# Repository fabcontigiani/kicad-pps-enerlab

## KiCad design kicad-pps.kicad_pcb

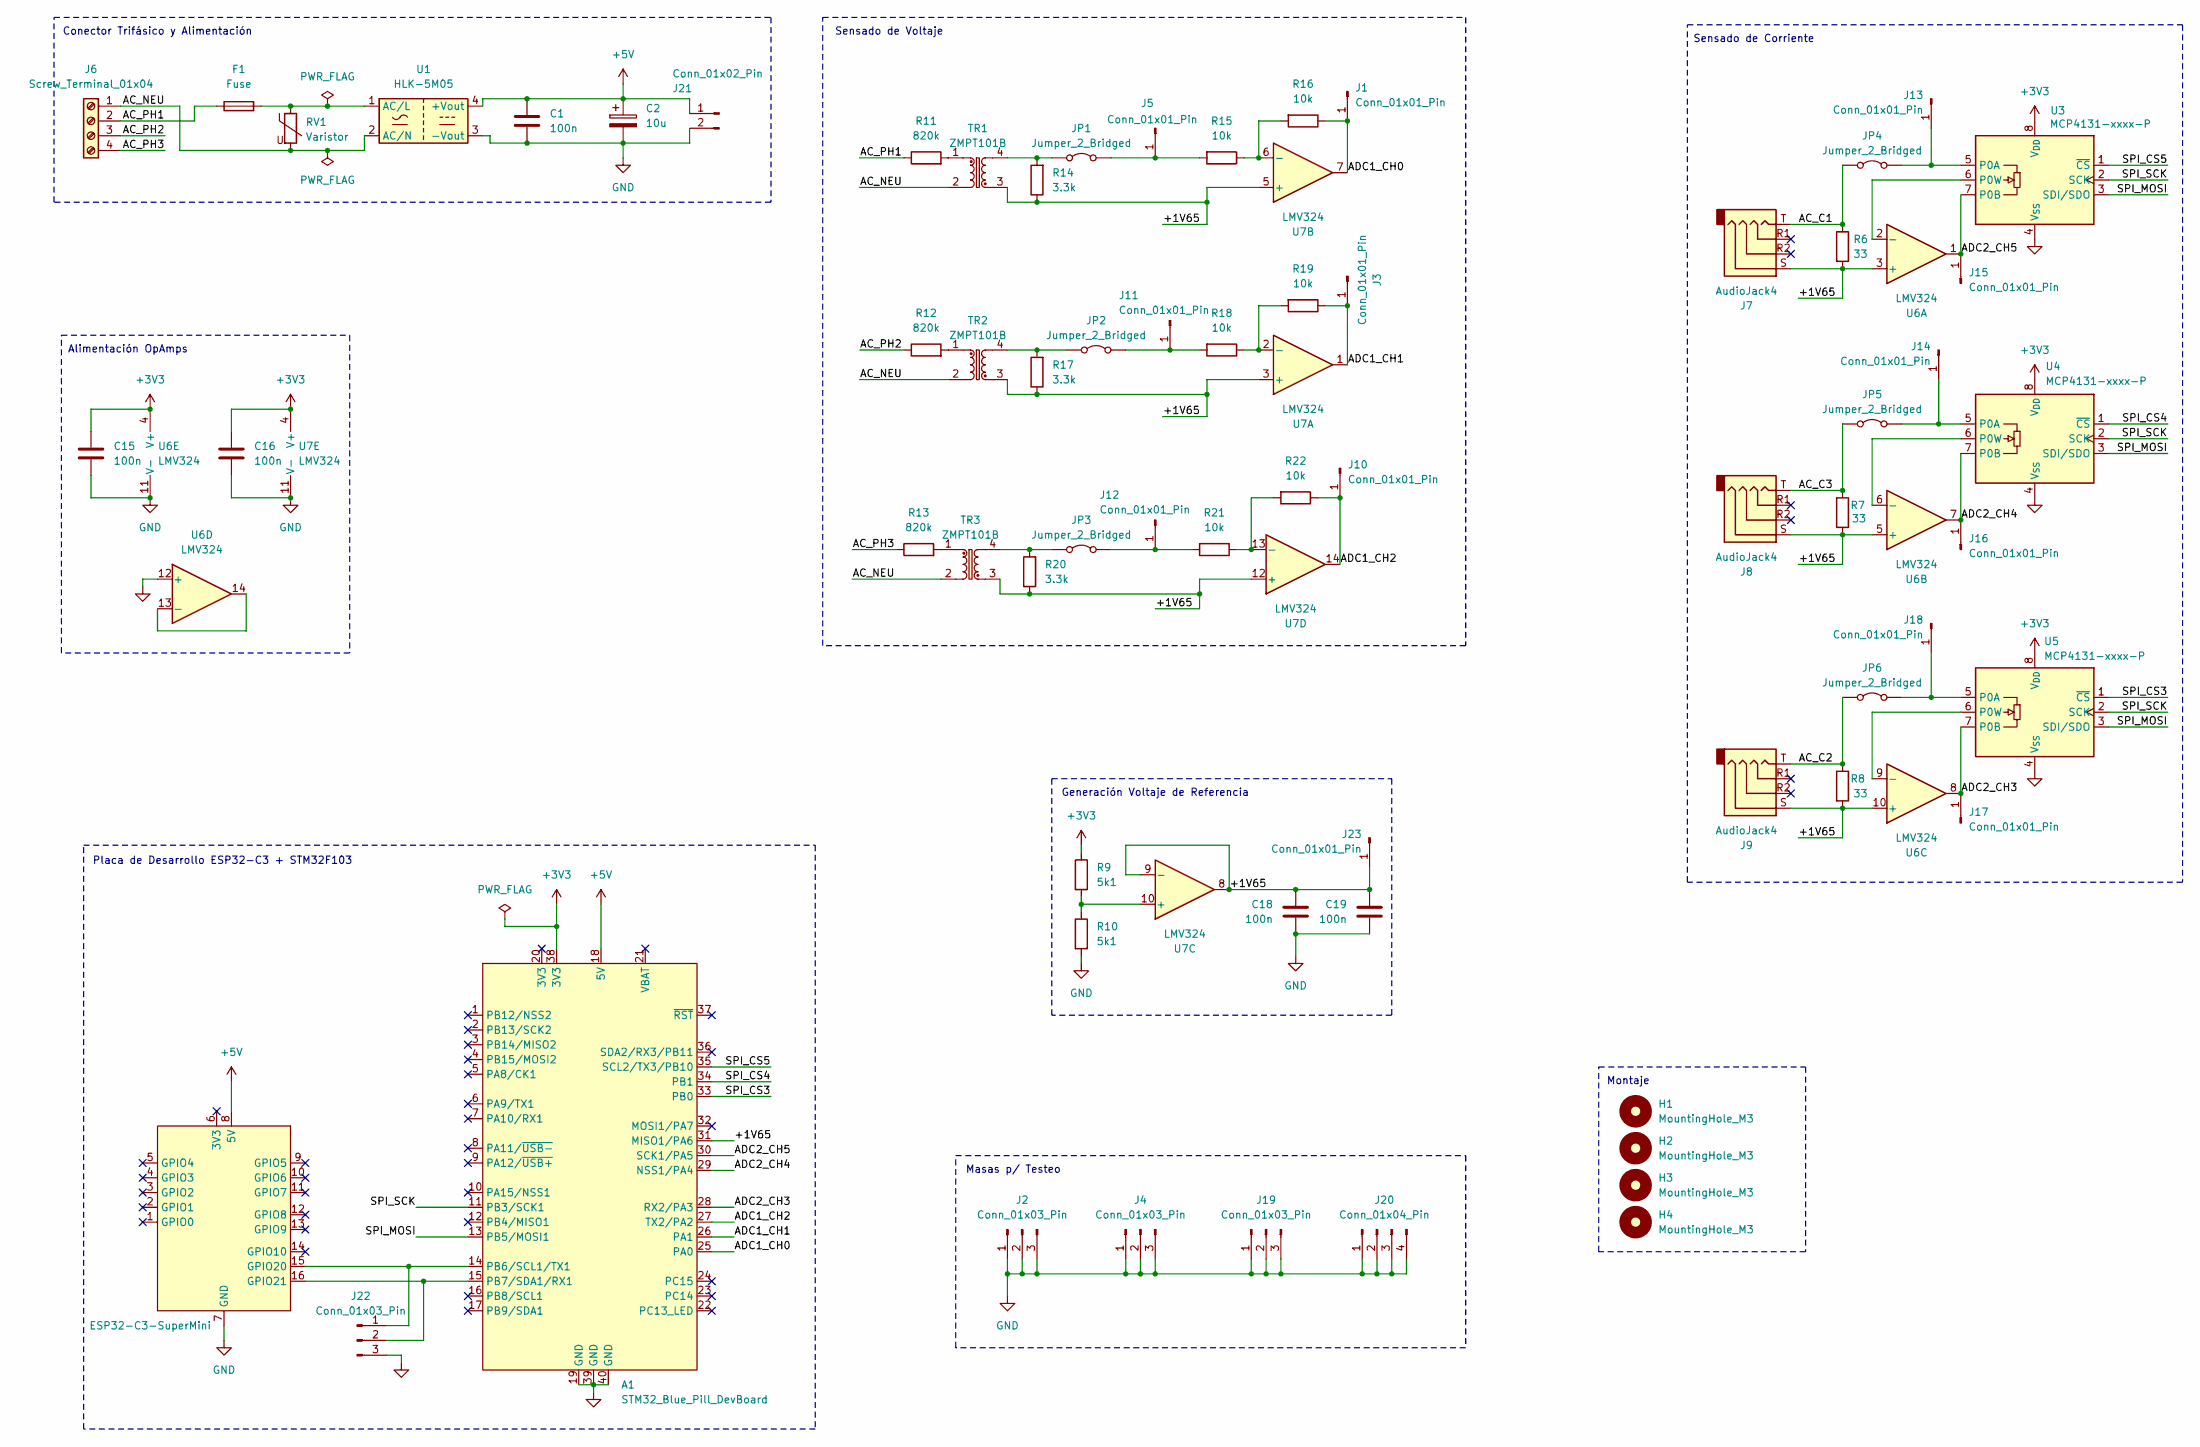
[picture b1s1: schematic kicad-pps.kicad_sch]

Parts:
A1: STM32_Blue_Pill_DevBoard
C1, C15, C16, C18, C19: 100n; CP_Radial_Tantal_D5.5mm_P2.50mm
C2: 10u; CP_Radial_D6.3mm_P2.50mm
F1: Fuse; Fuseholder_Clip-5x20mm_Littelfuse_445-030_Inline_P20.50x5.2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
H1, H2, H3, H4: MountingHole_M3; MountingHole_3.2mm_M3
J1, J3, J5, J10, J11, J12, J13, J14, J15, J16, J17, J18, J23: Conn_01x01_Pin; PinHeader_1x01_P2.54mm_Vertical
J2, J4, J19, J22: Conn_01x03_Pin; PinHeader_1x03_P2.54mm_Vertical
J6: Screw_Terminal_01x04; TerminalBlock_MaiXu_MX126-5.0-04P_1x04_P5.00mm
J7, J8, J9: AudioJack4; PinSocket_1x04_P2.54mm_Vertical
J20: Conn_01x04_Pin; PinHeader_1x04_P2.54mm_Vertical
J21: Conn_01x02_Pin; Molex_KK-396_5273-02A_1x02_P3.96mm_Vertical
JP1, JP2, JP3, JP4, JP5, JP6: Jumper_2_Bridged; TestPoint_2Pads_Pitch2.54mm_Drill0.8mm
R6, R7, R8: 33; R_Axial_DIN0207_L6.3mm_D2.5mm_P10.16mm_Horizontal
R9, R10: 5k1; R_Axial_DIN0207_L6.3mm_D2.5mm_P10.16mm_Horizontal
R11, R12, R13: 820k; R_Axial_DIN0207_L6.3mm_D2.5mm_P10.16mm_Horizontal
R14, R17, R20: 3.3k; R_Axial_DIN0207_L6.3mm_D2.5mm_P10.16mm_Horizontal
R15, R16, R18, R19, R21, R22: 10k; R_Axial_DIN0207_L6.3mm_D2.5mm_P10.16mm_Horizontal
RV1: Varistor; RV_Disc_D12mm_W3.9mm_P7.5mm
TR1, TR2, TR3: ZMPT101B; Transformer_Zeming_ZMPT101B
U1: HLK-5M05; Converter_ACDC_Hi-Link_HLK-5Mxx
U2: ESP32-C3-SuperMini
U3, U4, U5: MCP4131-xxxx-P; DIP-8_W7.62mm
U6, U7: LMV324; SOIC-14_3.9x8.7mm_P1.27mm

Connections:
+3V3: A1.38 (3V3), C15.1, C16.1, R9.1, U3.8 (V_{DD}), U4.8 (V_{DD}), U5.8 (V_{DD}), U6.4 (V+), U7.4 (V+)
+5V: A1.18 (5V), C1.1, C2.1, J21.1, U1.4 (+Vout), U2.8 (5V)
/+1V65: A1.31 (MISO1/PA6), C18.1, C19.1, J7.S, J8.S, J9.S, J23.1 (Pin_1_1), R6.2, R7.2, R8.2, R14.1, R17.1, R20.1, TR1.3, TR2.3, TR3.3, U6.3 (+), U6.5 (+), U6.10 (+), U7.3 (+), U7.5 (+), U7.8, U7.9 (-), U7.12 (+)
/AC_C1: J7.T, JP4.1 (A), R6.1
/AC_C2: J9.T, JP6.1 (A), R8.1
/AC_C3: J8.T, JP5.1 (A), R7.1
/AC_NEU: J6.1, RV1.2, TR1.2, TR2.2, TR3.2, U1.2 (AC/N)
/AC_PH1: F1.1, J6.2, R11.1
/AC_PH2: J6.3, R12.1
/AC_PH3: J6.4, R13.1
/ADC1_CH0: A1.25 (PA0), J1.1 (Pin_1_1), R16.1, U7.7
/ADC1_CH1: A1.26 (PA1), J3.1 (Pin_1_1), R19.1, U7.1
/ADC1_CH2: A1.27 (TX2/PA2), J10.1 (Pin_1_1), R22.1, U7.14
/ADC2_CH3: A1.28 (RX2/PA3), J17.1 (Pin_1_1), U5.7 (P0B), U6.8
/ADC2_CH4: A1.29 (NSS1/PA4), J16.1 (Pin_1_1), U4.7 (P0B), U6.7
/ADC2_CH5: A1.30 (SCK1/PA5), J15.1 (Pin_1_1), U3.7 (P0B), U6.1
/SPI_CS3: A1.33 (PB0), U5.1 (~CS)
/SPI_CS4: A1.34 (PB1), U4.1 (~CS)
/SPI_CS5: A1.35 (SCL2/TX3/PB10), U3.1 (~CS)
/SPI_MOSI: A1.13 (PB5/MOSI1), U3.3 (SDI/SDO), U4.3 (SDI/SDO), U5.3 (SDI/SDO)
/SPI_SCK: A1.11 (PB3/SCK1), U3.2 (SCK), U4.2 (SCK), U5.2 (SCK)
GND: A1.19 (GND), A1.39 (GND), A1.40 (GND), C1.2, C2.2, C15.2, C16.2, C18.2, C19.2, J2.1, J2.2, J2.3, J4.1, J4.2, J4.3, J19.1, J19.2, J19.3, J20.1, J20.2, J20.3, J20.4, J21.2, J22.3, R10.2, U1.3 (-Vout), U2.7 (GND), U3.4 (V_{SS}), U4.4 (V_{SS}), U5.4 (V_{SS}), U6.11 (V-), U6.12 (+), U7.11 (V-)
unnamed: A1.14 (PB6/SCL1/TX1), J22.1, U2.15 (GPIO20)
unnamed: A1.15 (PB7/SDA1/RX1), J22.2, U2.16 (GPIO21)
unnamed: J5.1 (Pin_1_1), JP1.2 (B), R15.2
unnamed: J11.1 (Pin_1_1), JP2.2 (B), R18.2
unnamed: J12.1 (Pin_1_1), JP3.2 (B), R21.2
unnamed: J13.1 (Pin_1_1), JP4.2 (B), U3.5 (P0A)
unnamed: J14.1 (Pin_1_1), JP5.2 (B), U4.5 (P0A)
unnamed: J18.1 (Pin_1_1), JP6.2 (B), U5.5 (P0A)
unnamed: JP1.1 (A), R14.2, TR1.4
unnamed: JP2.1 (A), R17.2, TR2.4
unnamed: JP3.1 (A), R20.2, TR3.4
unnamed: R11.2, TR1.1
unnamed: R12.2, TR2.1
unnamed: R13.2, TR3.1
unnamed: F1.2, RV1.1, U1.1 (AC/L)
unnamed: U3.6 (P0W), U6.2 (-)
unnamed: U4.6 (P0W), U6.6 (-)
unnamed: U5.6 (P0W), U6.9 (-)
unnamed: U6.13 (-), U6.14
unnamed: R18.1, R19.2, U7.2 (-)
unnamed: R15.1, R16.2, U7.6 (-)
unnamed: R9.2, R10.1, U7.10 (+)
unnamed: R21.1, R22.2, U7.13 (-)

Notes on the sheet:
Placa de Desarrollo ESP32-C3 + STM32F103
Sensado de Corriente
Montaje
Conector Trifásico y Alimentación
Alimentación OpAmps
Sensado de Voltaje
Generación Voltaje de Referencia
Masas p/ Testeo

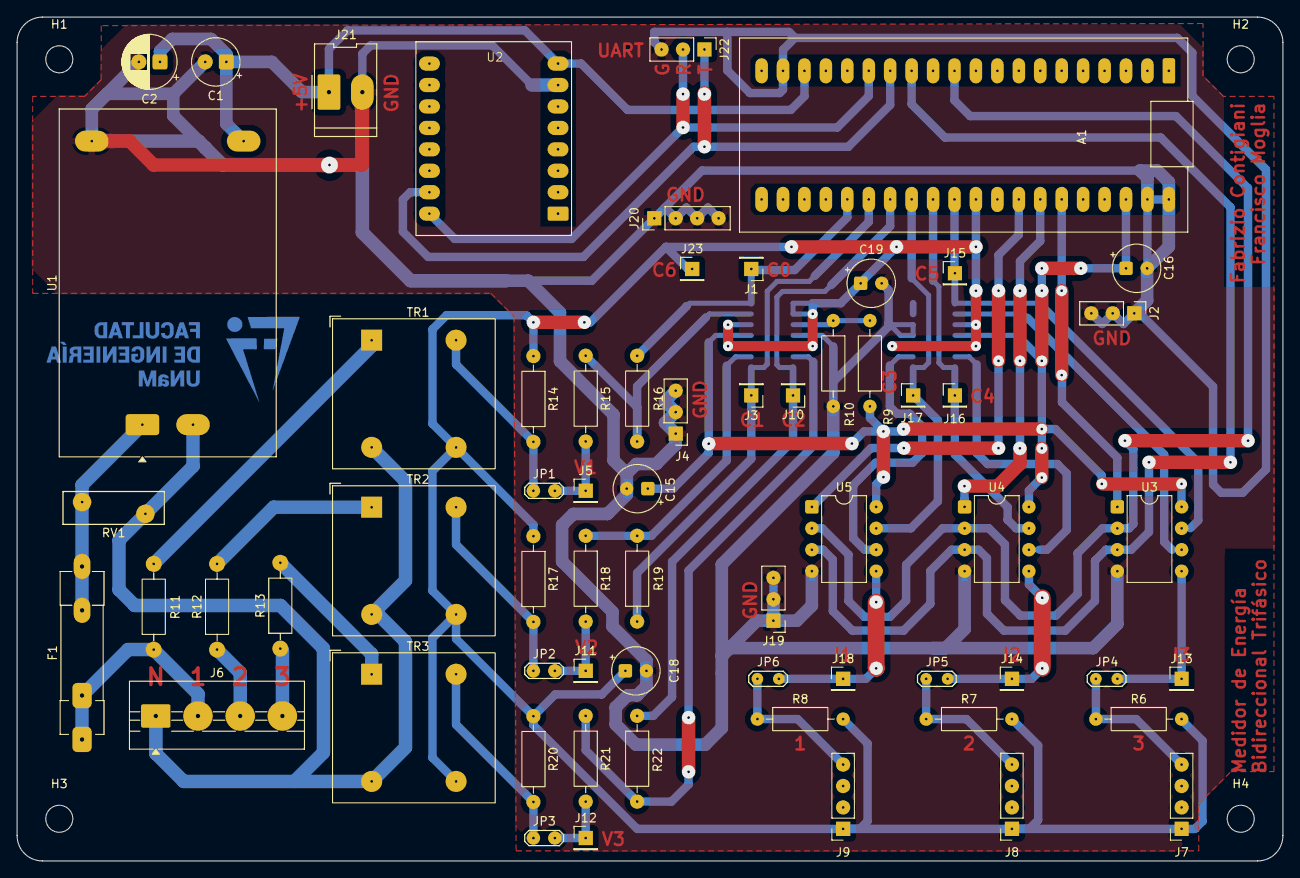
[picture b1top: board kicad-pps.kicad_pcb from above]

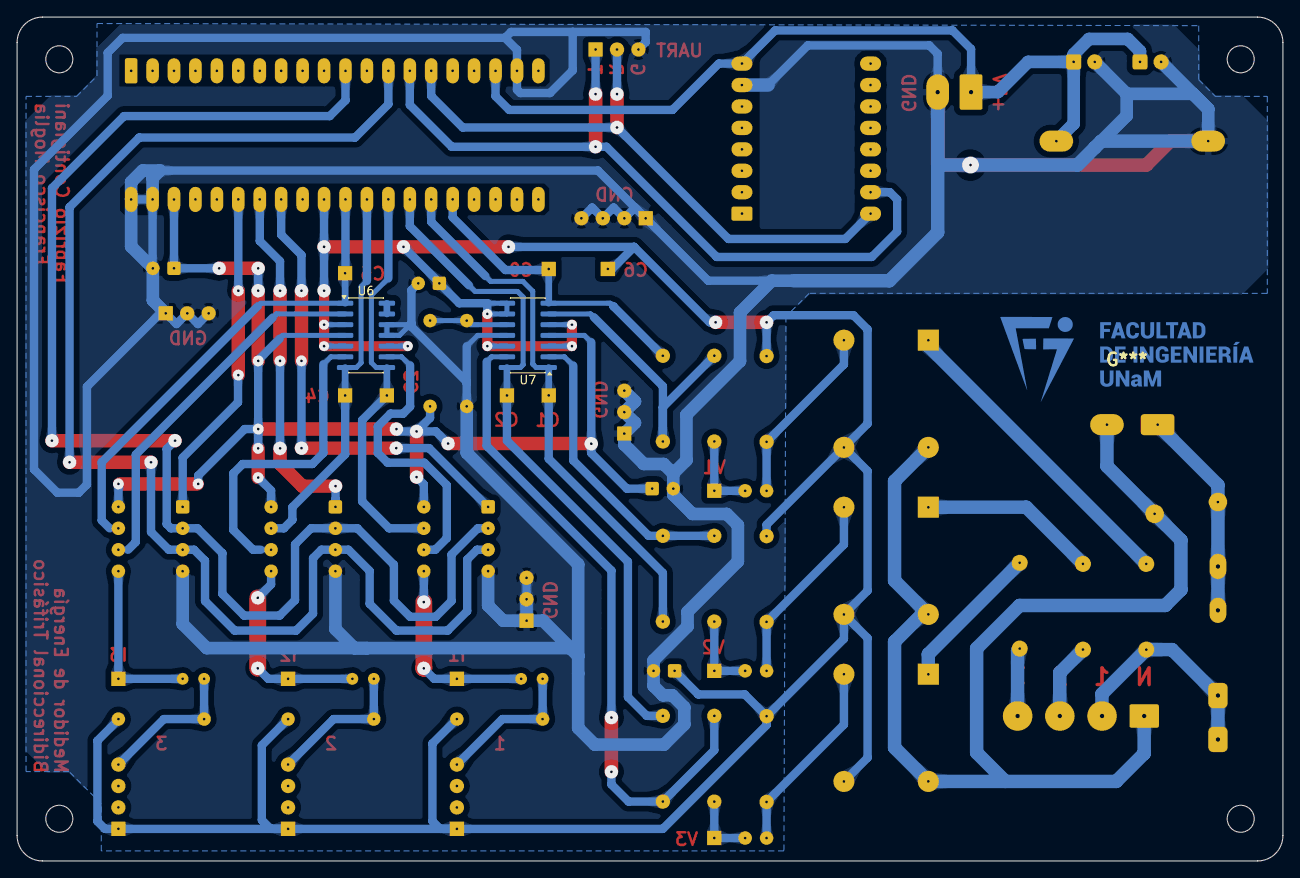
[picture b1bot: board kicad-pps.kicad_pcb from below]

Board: 2 copper layers, 150.0 x 100.0 mm, 69 parts (2 on the bottom side), 45 nets.

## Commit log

2026-04-27 initial fran commit
2026-05-04 Version 2: Bicapa
2026-05-05 branch completo-bicapa
2026-05-05 branch completo-unicapa wip
2026-05-06 completo unicapa
2026-05-06 mejoras
2026-05-07 fix erc
2026-05-07 fixes
2026-05-07 rev 2
2026-05-09 fix pdf
2026-05-11 add gerber
